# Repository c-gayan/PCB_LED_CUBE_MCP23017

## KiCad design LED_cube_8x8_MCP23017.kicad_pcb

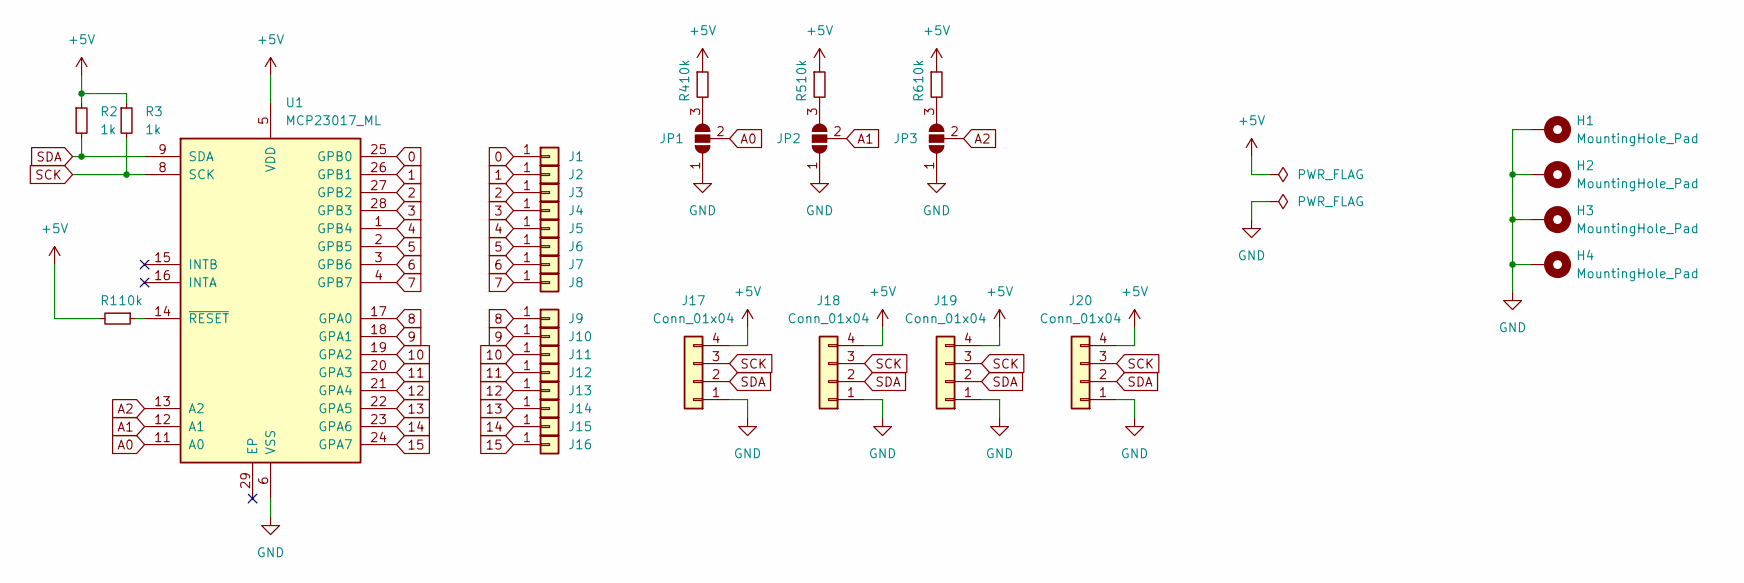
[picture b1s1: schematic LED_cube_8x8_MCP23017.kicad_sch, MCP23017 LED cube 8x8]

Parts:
H1, H2, H3, H4: MountingHole_Pad; MountingHole_3.5mm_Pad_Via
J1, J2, J3, J4, J5, J6, J7, J8, J9, J10, J11, J12, J13, J14, J15, J16: Conn_01x01; PinHeader_1x01_P2.54mm_Vertical
J17, J18: Conn_01x04; PinHeader_1x04_P2.54mm_Horizontal
J19, J20: Conn_01x04; PinSocket_1x04_P2.54mm_Horizontal
JP1, JP2, JP3: SolderJumper_3_Open; SolderJumper-3_P1.3mm_Open_RoundedPad1.0x1.5mm
R1, R4, R5, R6: 10k; R_0603_1608Metric
R2, R3: 1k; R_0603_1608Metric
U1: MCP23017_ML; QFN-28-1EP_6x6mm_P0.65mm_EP4.25x4.25mm

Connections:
0: J1.1, U1.25 (GPB0)
1: J2.1, U1.26 (GPB1)
2: J3.1, U1.27 (GPB2)
3: J4.1, U1.28 (GPB3)
4: J5.1, U1.1 (GPB4)
5: J6.1, U1.2 (GPB5)
6: J7.1, U1.3 (GPB6)
7: J8.1, U1.4 (GPB7)
8: J9.1, U1.17 (GPA0)
9: J10.1, U1.18 (GPA1)
10: J11.1, U1.19 (GPA2)
11: J12.1, U1.20 (GPA3)
12: J13.1, U1.21 (GPA4)
13: J14.1, U1.22 (GPA5)
14: J15.1, U1.23 (GPA6)
15: J16.1, U1.24 (GPA7)
+5V: J17.4, J18.4, J19.4, J20.4, R1.2, R2.1, R3.1, R4.1, R5.1, R6.1, U1.5 (VDD)
A0: JP1.2 (C), U1.11 (A0)
A1: JP2.2 (C), U1.12 (A1)
A2: JP3.2 (C), U1.13 (A2)
GND: H1.1, H2.1, H3.1, H4.1, J17.1, J18.1, J19.1, J20.1, JP1.1 (A), JP2.1 (A), JP3.1 (A), U1.6 (VSS)
unnamed: JP1.3 (B), R4.2
unnamed: JP2.3 (B), R5.2
unnamed: JP3.3 (B), R6.2
unnamed: R1.1, U1.14 (~RESET)
SCK: J17.3, J18.3, J19.3, J20.3, R3.2, U1.8 (SCK)
SDA: J17.2, J18.2, J19.2, J20.2, R2.2, U1.9 (SDA)

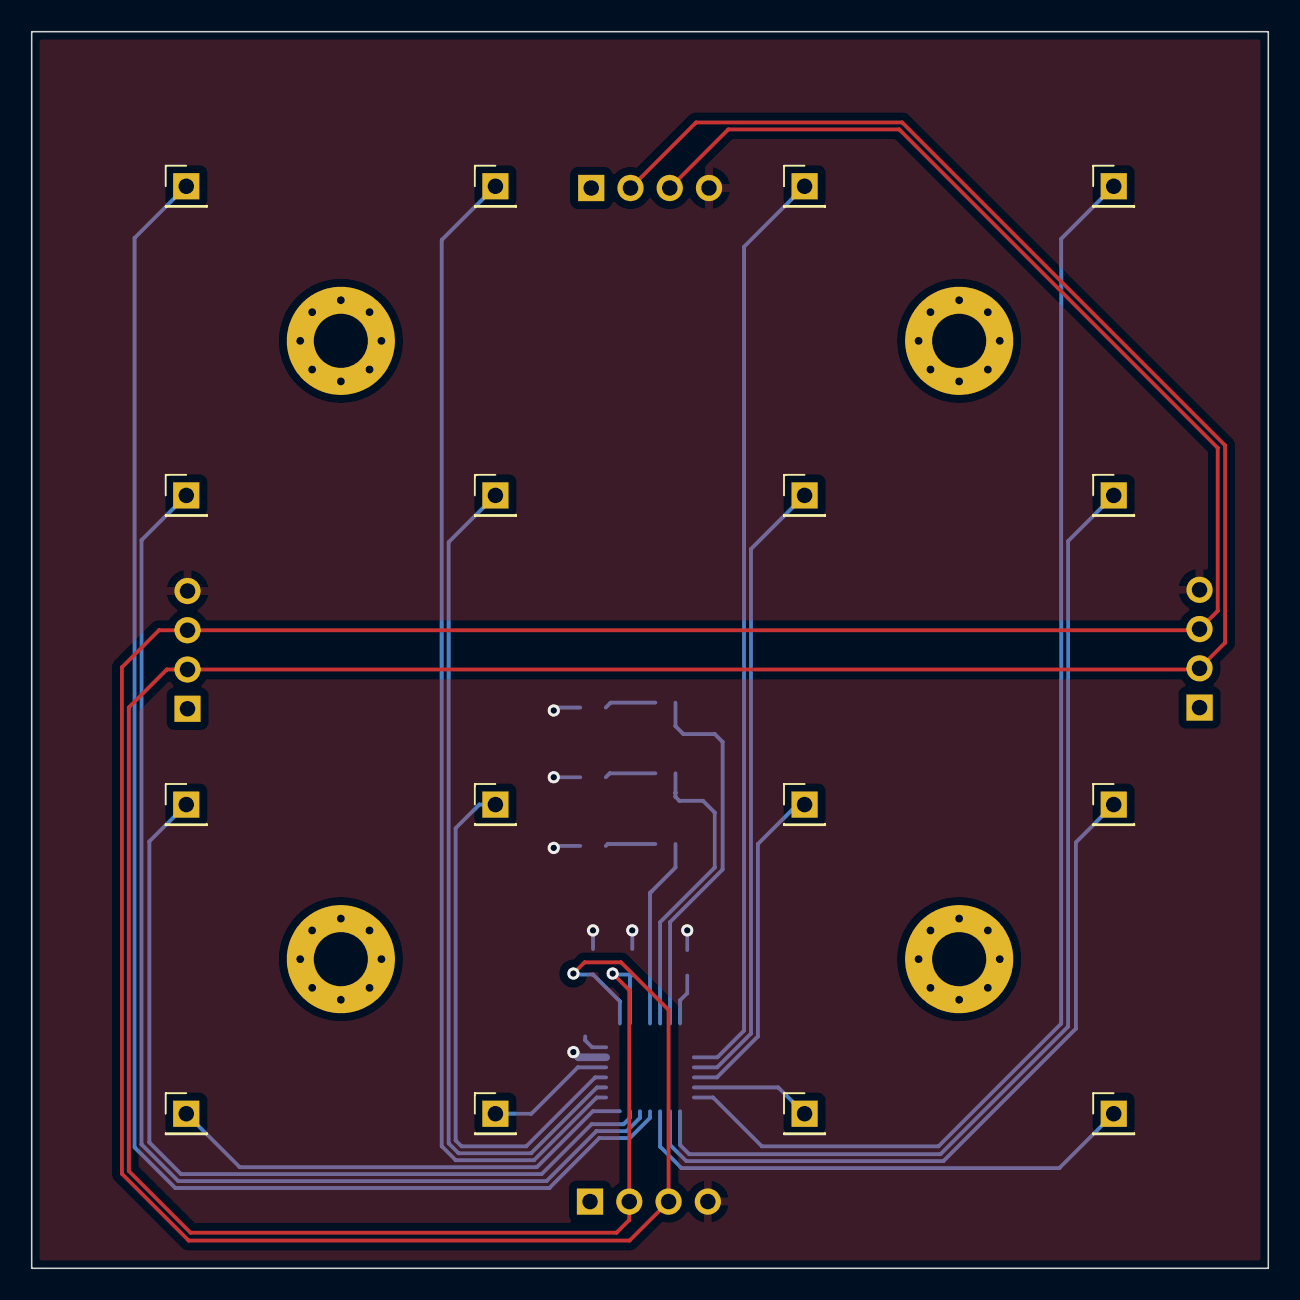
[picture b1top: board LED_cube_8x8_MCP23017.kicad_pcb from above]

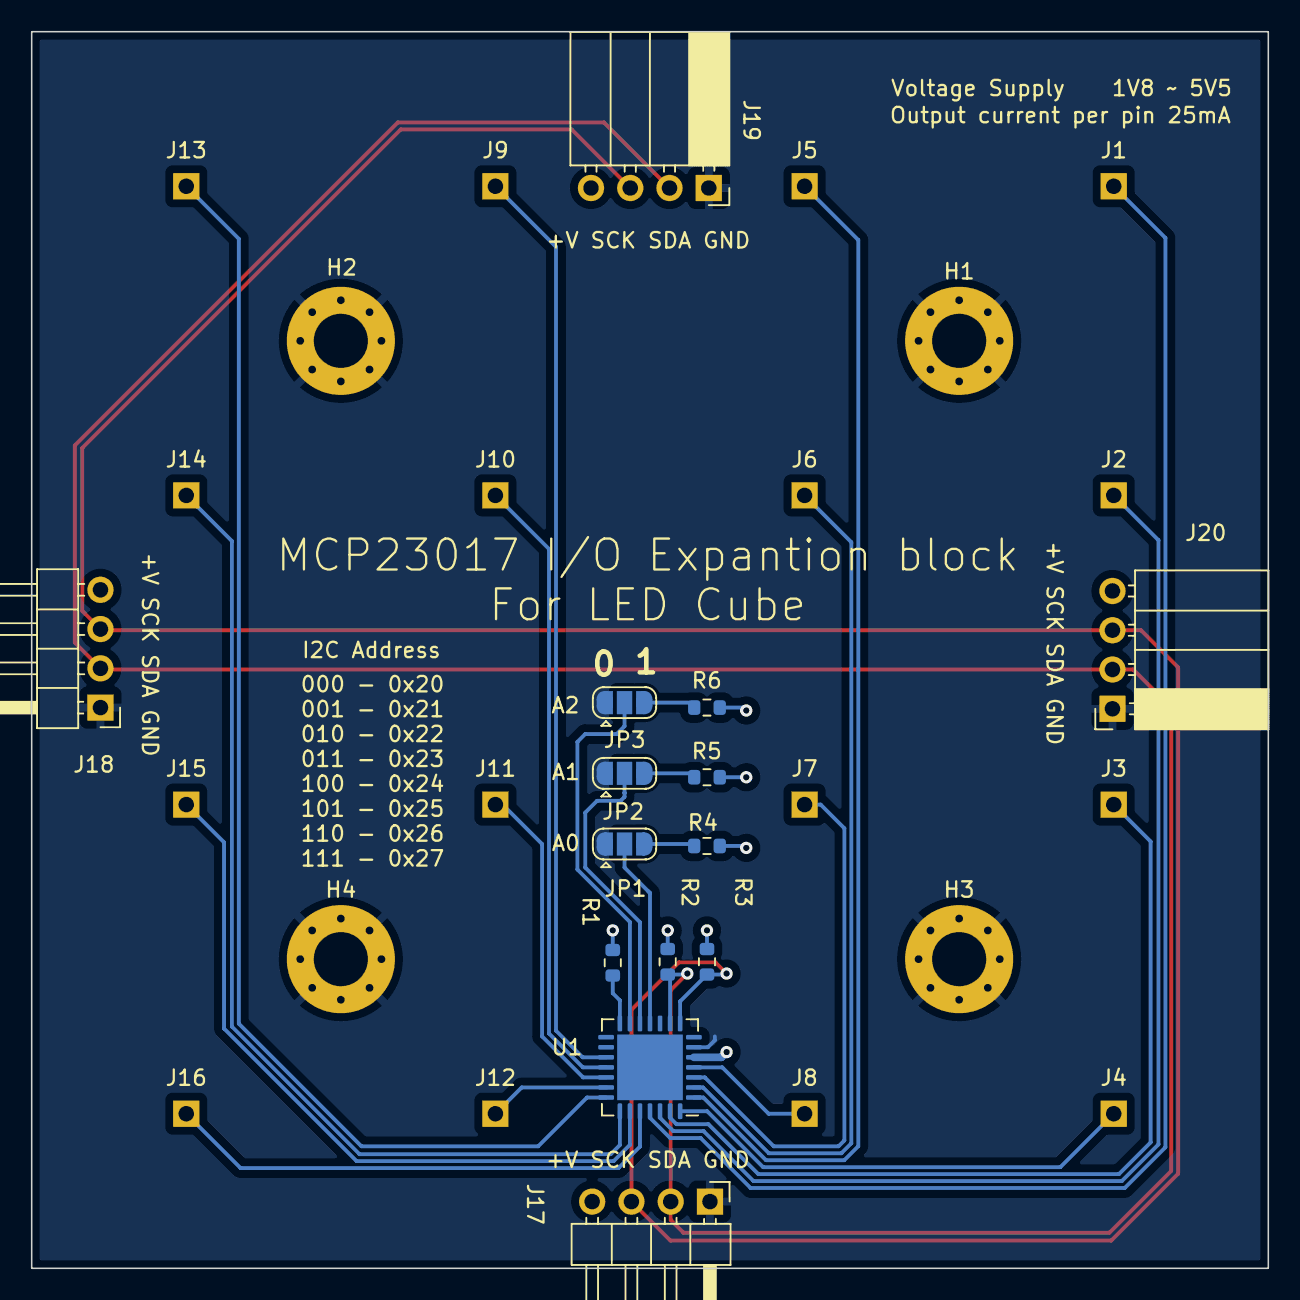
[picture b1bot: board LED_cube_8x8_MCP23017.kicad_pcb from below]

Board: 2 copper layers, 80.0 x 80.0 mm, 34 parts (18 on the bottom side), 27 nets.

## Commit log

2022-01-18 initiate
